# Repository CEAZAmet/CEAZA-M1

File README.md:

# Welcome to CEAZA-M1!
Wireless communication and memory backup expansion board for CEAZA MEGA.

## What is the CEAZA M1?

This design is an expansion board for CEAZA MEGA datalogger, which add the local wireless comumunication capability to the system.
The board Design integrates:
* An Ra-02 Ai-Thinker for 410-525MHz or Ra-01SH for 803MHz~930MHz LoRa Radio module.
* An ATGM336H-5N-31 GNSS GPS BDS positioning and navigation module.
* An ESP-12E WiFi module.
* A W25N01GVZEIG 1G-bit serial nand flash memory for redundant data storage.

All modules integratred are equiped with its respective power switch and power supply controlled by firmware for energy save when low power consumtions are required.
An on board jumper is included, ready to solder when the backup power source is required for GNSS module from permanent 3.3V available from CEAZA MEGA board, which increases 10uA the system power consumption.

The GNSS and WiFi modules share the same MCU UART2 thought an 74HC4052D analog multiplexer, which is controlled by firmware.

This board is pin compatible and should be connected to the CEAZA MEGA system to proper work.

## Documentation
A comprehensive documentation for well undertand, use or modify the CEAZA M1 board is available in our Wiki. In adition, we share with you the schematics diagrams, adns Arduino example codes.

## Quickstart guide
Install the M1 board in the CEAZA MEGA's bottom, make certain connection throuhg the boards by three 2 x 10 pin header terminals is rigth. 
Attach GNSS and LoRa antennas to the board, connect the power source 7 to 14 Vdc to the system.
Connect the CEAZA MEGA main board system to the host PC by mini-USB connector, open the Arduino ide software, select the Arduino Mega board and the correspondign COM port.

Open any of examples scketches and upload to the board.

# Contact and support
For all kinds of inquiries, please contact me to my e-mail address: adrian.gallardo@ceaza.cl

# Contributing
You are welcome to contribute to the development or improvement of M1 hardware design or example application codes. Feel free to submit a new pull request via github.

# Academic Context

# Licensing

# Disclaimer
Use M1 board and examples code at your own risk. We do not encourage any malicious use of our board.

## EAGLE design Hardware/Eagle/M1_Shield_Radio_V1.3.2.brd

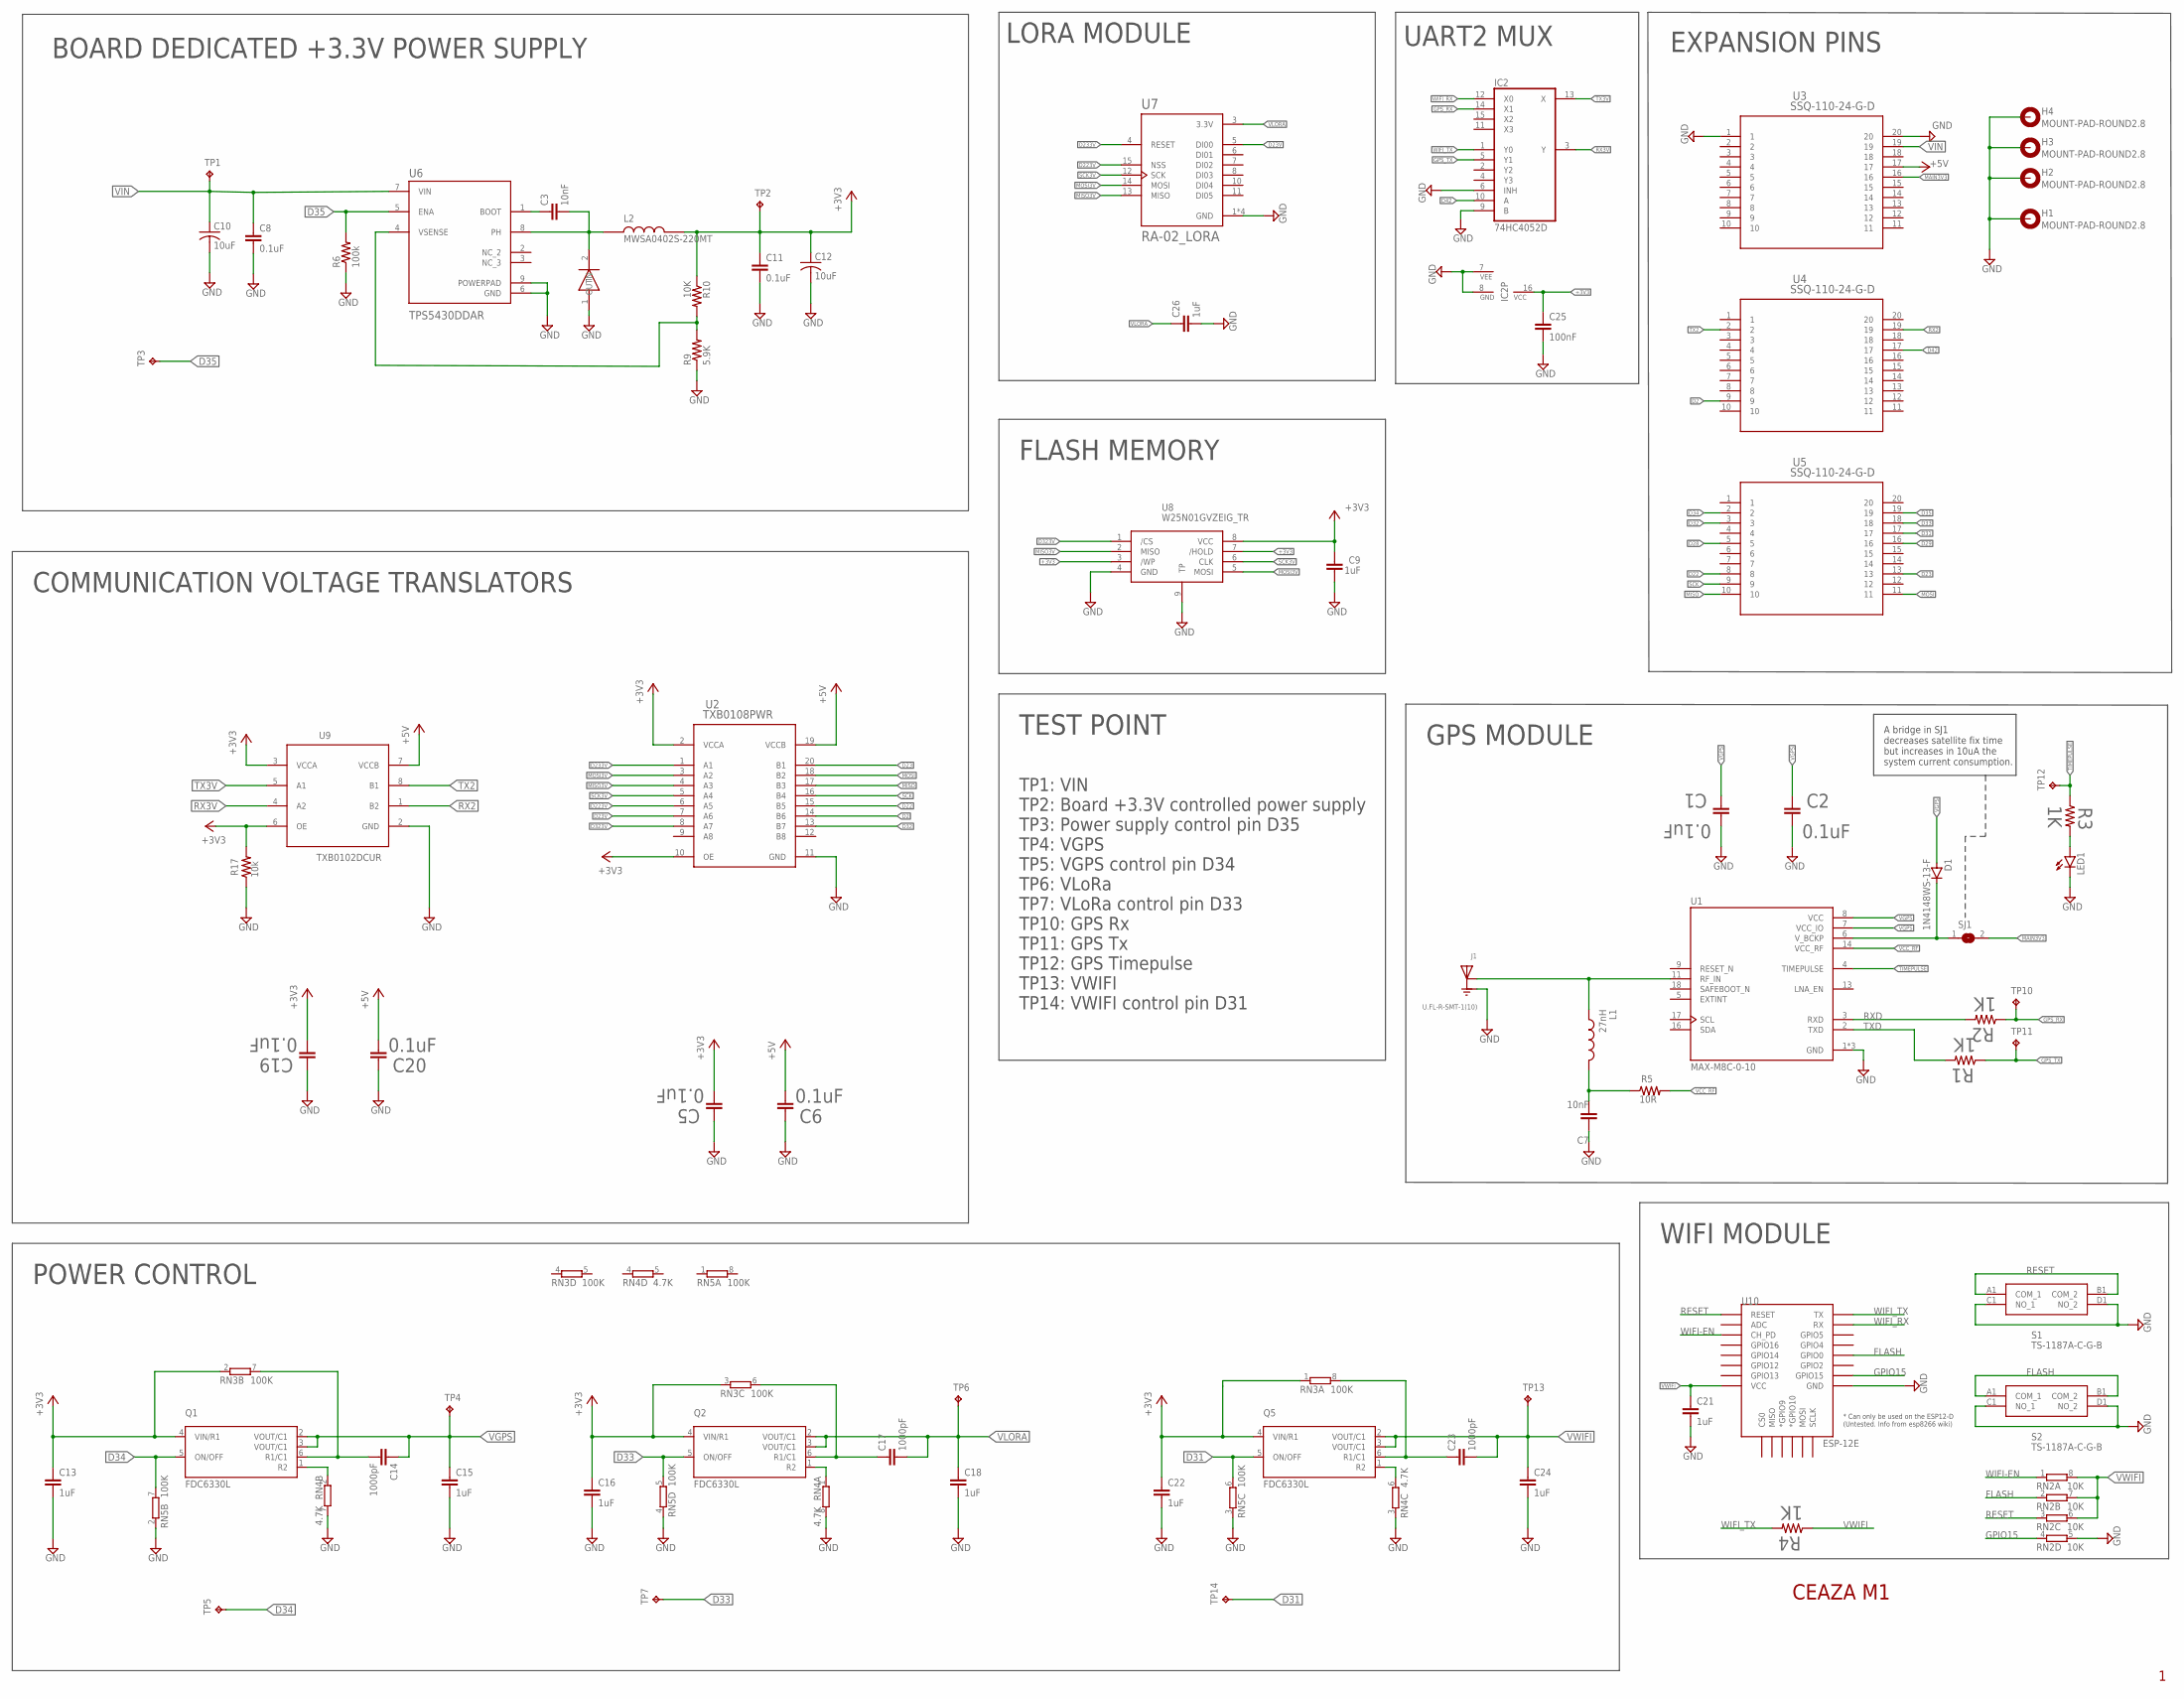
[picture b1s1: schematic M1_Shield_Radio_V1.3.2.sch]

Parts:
C1, C2, C5, C6, C8, C11, C19, C20: 0.1uF; C0603K
C3, C7: 10nF; C0603K
C9, C13, C15, C16, C18, C21, C22, C24, C26: 1uF; C0603K
C10, C12: 10uF; C0603K
C14, C17, C23: 1000pF; C0603K
C25: 100nF; C0603K
D1: 1N4148WS-13-F; SOD323-W
H1, H2, H3, H4: MOUNT-PAD-ROUND2.8; 2,8-PAD
IC2: 74HC4052D; SO16
J1: U.FL-R-SMT-1(10); HRS_U.FL-R-SMT-1(10)
L1: 27nH; INDC1005X55N
L2: MWSA0402S-220MT
LED1: LEDCHIP-LED0805; CHIP-LED0805
Q1, Q2, Q5: FDC6330L; SOT95P280X110-6N
R1, R2, R3, R4: 1K; R0603
R5: 10R; R0603
R6: 100k; R0603
R9: 5.9K; R0603
R10: 10K; R0603
R17: 10k; R0603
RN2: 10K; 0603-ARV
RN3, RN5: 100K; 0603-ARV
RN4: 4.7K; 0603-ARV
S1, S2: TS-1187A-C-G-B; TS1187ACGB
SJ1: SJ
TP1, TP2, TP3, TP4, TP5, TP6, TP7, TP10, TP11, TP12, TP13, TP14: TPB1,27; B1,27
U1: MAX-M8C-0-10; XCVR_MAX-M8C-0-10
U2: TXB0108PWR; PW0020A_N
U3, U4, U5: SSQ-110-24-G-D; 1-215307-0
U6: TPS5430DDAR; CONV_TPS5430DDAR
U7: RA-02_LORA; MODULE_RA-02_LORA
U8: W25N01GVZEIG_TR; W25N01GVZEIGTR
U9: TXB0102DCUR; DCU0008A_L
U10: ESP-12E; ESP12E-SMD
U$1: SMA-SS34

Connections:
+3V3: C5.2, C9.1, C11.1, C12.1, C13.1, C16.1, C19.2, C22.1, C25.1, IC2.16 (VCC), L2.P$2, Q1.4 (VIN/R1), Q2.4 (VIN/R1), Q5.4 (VIN/R1), R10.1, R17.2, RN3.1, RN3.2 (1), RN3.3 (1), TP2.TP, U2.2 (VCCA), U2.10 (OE), U8.3 (/WP), U8.7 (/HOLD), U8.8 (VCC), U9.3 (VCCA), U9.6 (OE)
+5V: C6.2, C20.2, U2.19 (VCCB), U3.17, U9.7 (VCCB)
D2: U2.14 (B6), U4.9
D22: U2.15 (B5), U5.8
D23: U2.20 (B1), U5.13
D23V: U2.7 (A6), U7.5 (DI00)
D28: U5.5
D29: U5.16
D31: Q5.5 (ON/OFF), RN5.6 (2), TP14.TP, U5.17
D32: U2.13 (B7), U5.3
D33: Q2.5 (ON/OFF), RN5.5 (2), TP7.TP, U5.18
D34: Q1.5 (ON/OFF), RN5.7 (2), TP5.TP, U5.2
D35: R6.2, TP3.TP, U5.19, U6.5 (ENA)
D42: IC2.10 (A), U4.17
D223V: U2.6 (A5), U7.15 (NSS)
D233V: U2.1 (A1), U7.4 (RESET)
D323V: U2.8 (A7), U8.1 (/CS)
FLASH: RN2.2 (1), S2.A1 (COM_1), S2.B1 (COM_2), U10.GPIO0
GND: C1.1, C2.1, C5.1, C6.1, C7.1, C8.2, C9.2, C10.2, C11.2, C12.2, C13.2, C15.2, C16.2, C18.2, C19.1, C20.1, C21.2, C22.2, C24.2, C25.2, C26.2, H1.B2,8, H2.B2,8, H3.B2,8, H4.B2,8, IC2.6 (INH), IC2.7 (VEE), IC2.8 (GND), IC2.9 (B), J1.1 (GND), J1.3 (GND), LED1.C, R6.1, R9.1, R17.1, RN2.5 (2), RN4.3 (1), RN4.7 (2), RN4.8 (2), RN5.2 (1), RN5.3 (1), RN5.4 (1), S1.C1 (NO_1), S1.D1 (NO_2), S2.C1 (NO_1), S2.D1 (NO_2), U1.1 (GND), U1.10 (GND), U1.12 (GND), U2.11 (GND), U3.1, U3.20, U6.6 (GND), U6.9 (POWERPAD), U7.1 (GND), U7.2 (GND), U7.9 (GND), U7.16 (GND), U8.4 (GND), U8.9 (TP), U9.2 (GND), U10.GND, U$1.1 (IN)
GPIO15: RN2.4 (1), U10.GPIO15
GPS_RX: IC2.14 (X1), R2.1, TP10.TP
GPS_TX: IC2.5 (Y1), R1.1, TP11.TP
MAIN3V3: SJ1.2, U3.16
MISO: U2.17 (B3), U5.10
MISO3V: U2.4 (A3), U7.13 (MISO), U8.2 (MISO)
MOSI: U2.18 (B2), U5.11
MOSI3V: U2.3 (A2), U7.14 (MOSI), U8.5 (MOSI)
unnamed: Q5.1 (R2), RN4.6 (2)
unnamed: LED1.A, R3.2
unnamed: J1.2 (SIG), L1.1, U1.11 (RF_IN)
unnamed: C7.2, L1.2, R5.1
unnamed: C3.1, U6.1 (BOOT)
unnamed: C14.2, Q1.6 (R1/C1), RN3.7 (2)
unnamed: C23.1, Q5.6 (R1/C1), RN3.8 (2)
unnamed: Q1.1 (R2), RN4.2 (1)
unnamed: Q2.1 (R2), RN4.1
unnamed: C17.1, Q2.6 (R1/C1), RN3.6 (2)
unnamed: D1.C, SJ1.1, U1.6 (V_BCKP)
unnamed: C3.2, L2.P$1, U6.8 (PH), U$1.2 (OUT)
RESET: RN2.3 (1), S1.A1 (COM_1), S1.B1 (COM_2), U10.RESET
RX2: U4.19, U9.1 (B2)
RX3V: IC2.3 (Y), U9.4 (A2)
RXD: R2.2, U1.3 (RXD)
SCK: U2.16 (B4), U5.9
SCK3V: U2.5 (A4), U7.12 (SCK), U8.6 (CLK)
TIMEPULSE: R3.1, TP12.TP, U1.4 (TIMEPULSE)
TX2: U4.2, U9.8 (B1)
TX3V: IC2.13 (X), U9.5 (A1)
TXD: R1.2, U1.2 (TXD)
VCC_RF: R5.2, U1.14 (VCC_RF)
VFB: R9.2, R10.2, U6.4 (VSENSE)
VGPS: C1.2, C2.2, C14.1, C15.1, D1.A, Q1.2 (VOUT/C1), Q1.3 (VOUT/C1), TP4.TP, U1.7 (VCC_IO), U1.8 (VCC)
VIN: C8.1, C10.1, TP1.TP, U3.19, U6.7 (VIN)
VLORA: C17.2, C18.1, C26.1, Q2.2 (VOUT/C1), Q2.3 (VOUT/C1), TP6.TP, U7.3 (3.3V)
VWIFI: C21.1, C23.2, C24.1, Q5.2 (VOUT/C1), Q5.3 (VOUT/C1), R4.1, RN2.6 (2), RN2.7 (2), RN2.8 (2), TP13.TP, U10.VCC
WIFI-EN: RN2.1, U10.CH_PD
WIFI_RX: IC2.12 (X0), U10.RXD0 (RX)
WIFI_TX: IC2.1 (Y0), R4.2, U10.TXD0 (TX)

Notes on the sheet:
BOARD DEDICATED +3.3V POWER SUPPLY
LORA MODULE
FLASH MEMORY
POWER CONTROL
GPS MODULE
COMMUNICATION VOLTAGE TRANSLATORS
EXPANSION PINS
TP1: VIN TP2: Board +3.3V controlled power supply TP3: Power supply control pin D35 TP4: VGPS TP5: VGPS control pin D34 TP6: VLoRa TP7: VLoRa control pin D33 TP10: GPS Rx TP11: GPS Tx TP12: GPS Timepulse TP13: VWIFI TP14: VWIFI control pin D31
TEST POINT
UART2 MUX
WIFI MODULE
A bridge in SJ1 decreases satellite fix time but increases in 10uA the system current consumption.
CEAZA M1

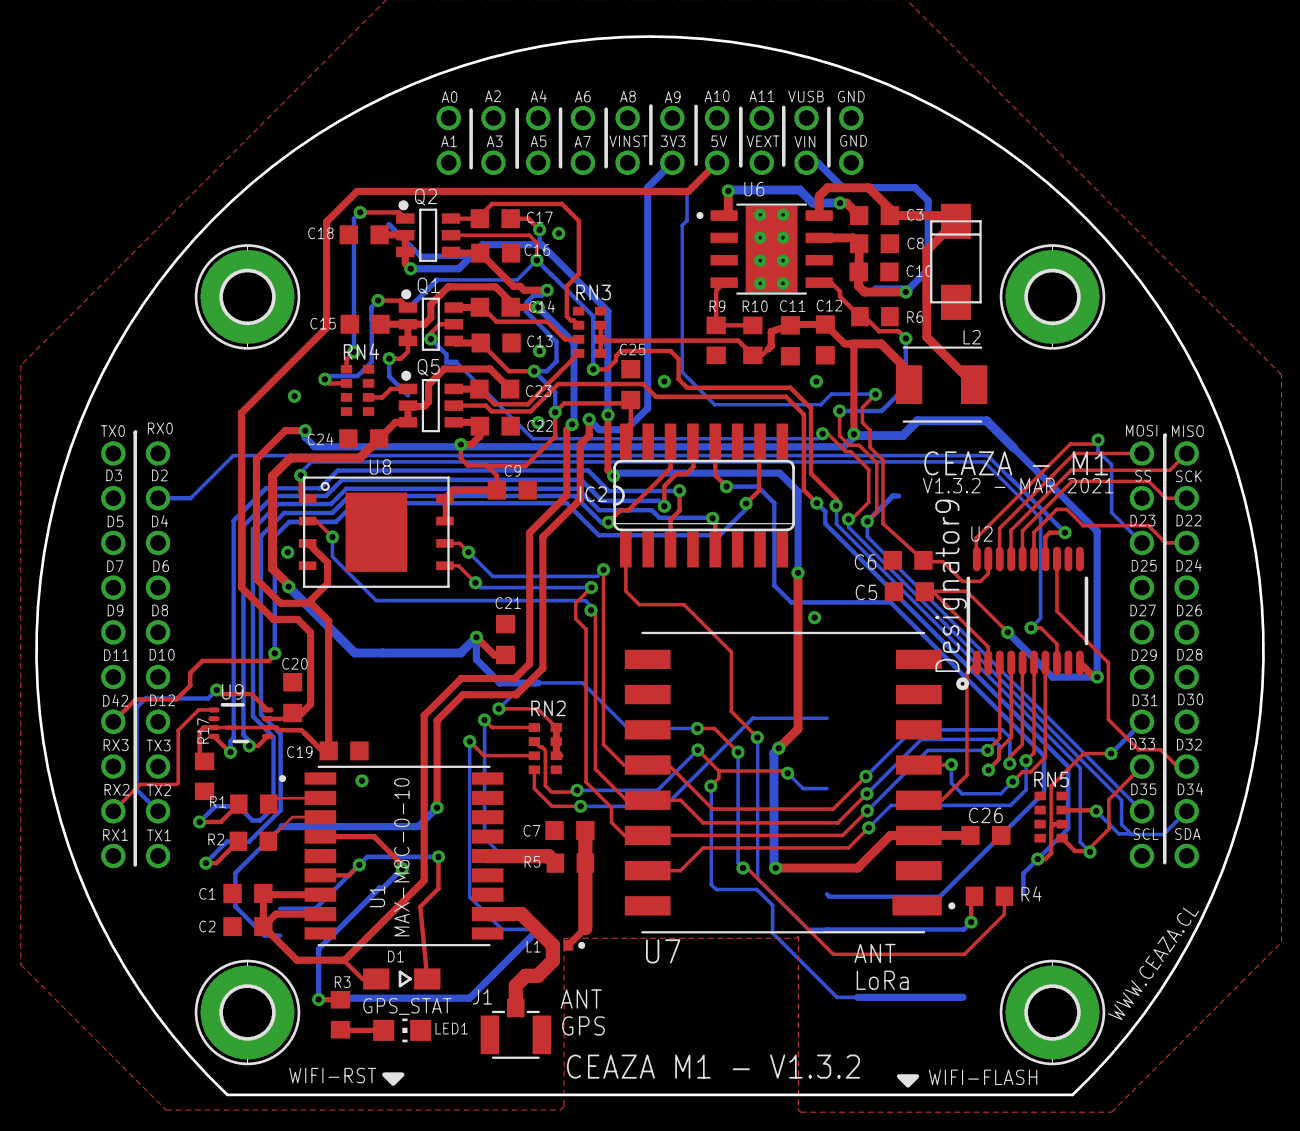
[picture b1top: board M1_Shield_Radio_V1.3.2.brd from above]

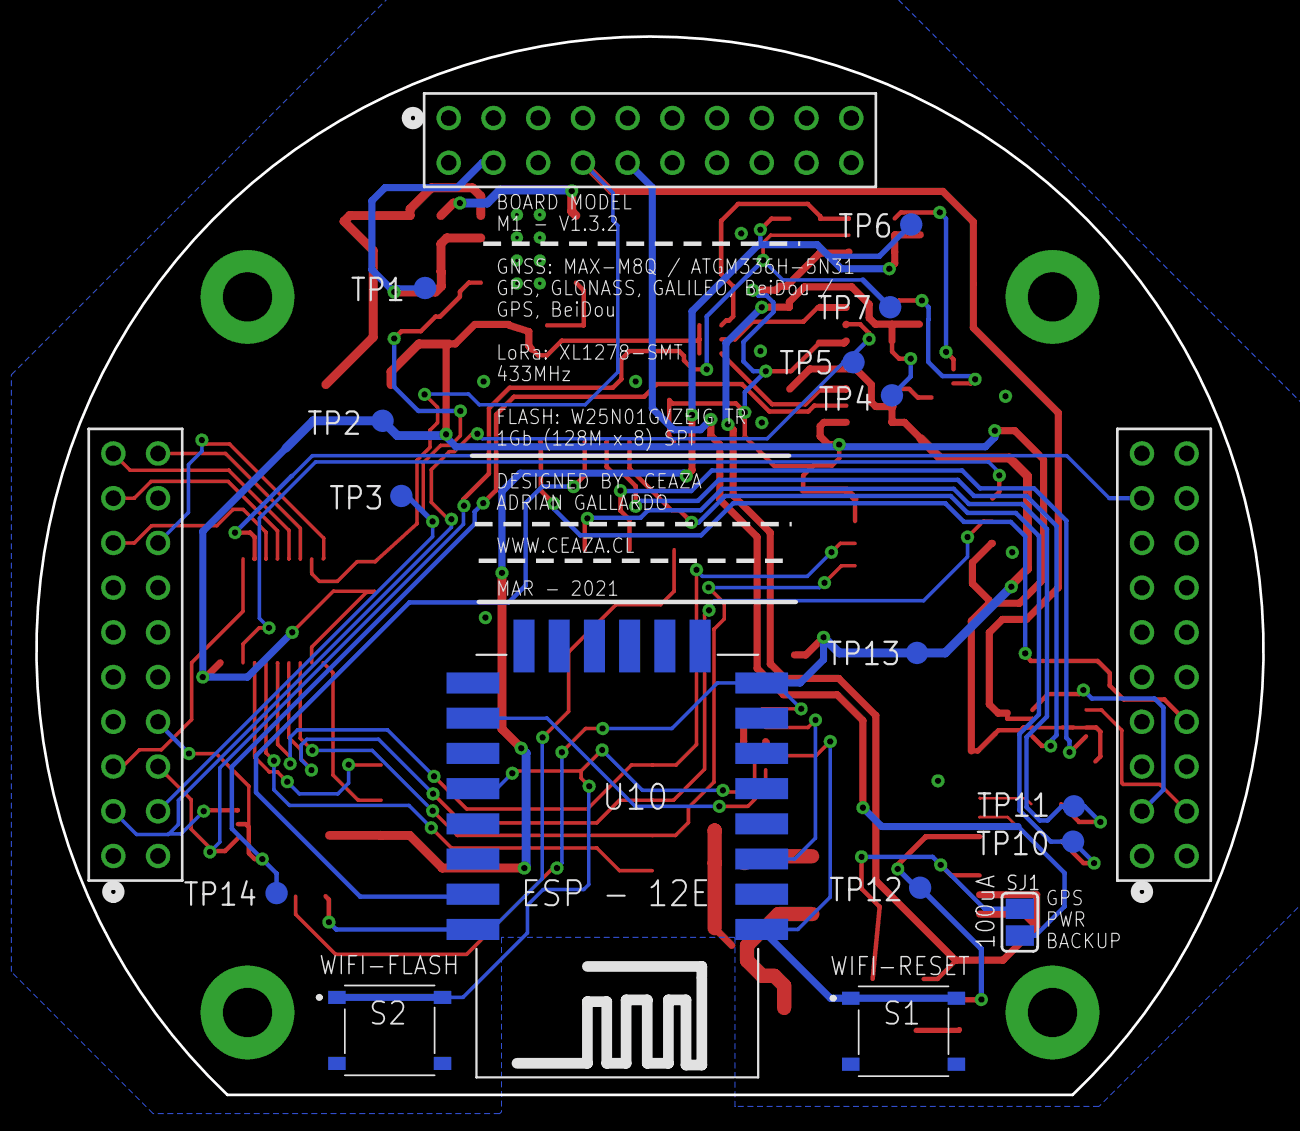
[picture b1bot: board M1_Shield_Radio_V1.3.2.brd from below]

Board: 2 copper layers, 69.7 x 60.1 mm, 77 parts (19 on the bottom side), 56 nets.

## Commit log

2021-09-13 Create examples
2021-09-13 Rename examples to Examples
2021-09-13 Rename M1_CM_GNSS_Monitor.ino to Examples/M1_CM_GNSS_Monitor/M1_CM_GNSS_Monitor.ino
